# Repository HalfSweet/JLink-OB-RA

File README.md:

# JLink-OB-RA

该工程实现了SEGGER的J-Link-OB-RA4M2硬件设计，并加入了UART和SWD接口的硬件SWAP功能。

## KiCAD工程

该工程使用KiCAD设计，需要使用8.0以上版本打开。

## 版权申明

该工程的原始设计文件由SEGGER提供，本工程仅复刻硬件设计。其中运行的软件部分由SEGGER提供，本工程不提供任何软件支持。

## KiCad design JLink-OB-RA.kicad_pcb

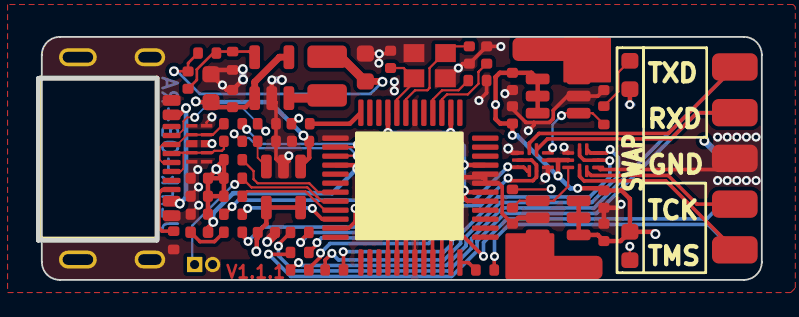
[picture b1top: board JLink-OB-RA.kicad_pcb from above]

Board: 4 copper layers, 40.1 x 13.3 mm, 57 parts (0 on the bottom side), 47 nets.

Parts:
C1, C4, C7, C8, C9, C13, C17: 0.1u; C_0402_1005Metric
C2, C3: 20p; C_0402_1005Metric
C5, C6: 50p; C_0402_1005Metric
C10: 22p; C_0402_1005Metric
C11, C16: 22u; C_0603_1608Metric
C12: 1u; C_0402_1005Metric
C14, C15, C18: 10u; C_0402_1005Metric
D1: LED; LED_0402_1005Metric
D2, D3: LED; LED_0603_1608Metric
J1: USB_C_Receptacle_USB2.0; USB-C-SMD_SHOU_TYPE-C-16P-CB1.6
J2: Conn_02x05_Counter_Clockwise; Conn_02x05_PinHeader_SMD
J3: Header; PinHeader_1x02_P1.00mm_Vertical
L1: 2.2u; L_1008_2520Metric
R1, R2, R5, R6, R7: 10k; R_0402_1005Metric
R3, R4: 27R; R_0402_1005Metric
R8, R19, R20: 1k; R_0402_1005Metric
R9, R10: 5.1k; R_0402_1005Metric
R11, R12, R13, R14, R15, R16: 150R; R_0402_1005Metric
R17: 100k; R_0402_1005Metric
R18: 22.1k; R_0402_1005Metric
R21: 6.8k; R_0402_1005Metric
TP1, TP2: TouchPad; Touch_SMD_BOX
U1: R7FA4M2AB3CFL#AA0; LQFP-48_7x7mm_P0.5mm
U2: ESD0524P_C2901307; DFN-10_L2.5-W1.0-P0.50-BL-A
U3, U4: TTP223; SOT-23-6
U5, U6: RS2227XUTQK10; WQFN-10_L1.8-W1.4-P0.40-BL
U7: MT3410; SOT-23-5
U8: MT9700; SOT-23-5
Y1: 12M; Crystal_SMD_2520-4Pin_2.5x2.0mm

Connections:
+3V3: C4.1, C7.1, C8.1, C9.1, C10.1, C11.1, C12.1, C13.1, C14.1, D1.2 (A), D2.2 (A), D3.2 (A), J2.8, L1.1, R2.1, R5.1, R6.1, R7.1, R17.1, U1.2 (VBATT), U1.9 (VCC_1), U1.16 (VCC_USB), U1.30 (VCC_2), U1.41 (VREFH), U1.42 (AVCC0), U1.45 (VREFH0), U3.4 (AHLB), U3.5 (VDD), U3.6 (TOG), U4.4 (AHLB), U4.5 (VDD), U4.6 (TOG), U5.9 (V+), U6.9 (V+)
+5V: C16.1, C17.1, C18.2, U7.1 (EN), U7.4 (VIN), U8.1 (VOUT)
/#RESET: J2.6, R15.2
/BOOT: J3.1, R6.2, U1.20 (P201/MD)
/EXTAL: C3.1, U1.8 (P212/EXTAL), Y1.3
/RA_RST: R5.2, U1.19 (RES)
/RX: U1.23 (P301), U6.4 (HSD1-), U6.7 (HSD2+)
/R_RX: J2.4, U6.1 (D+)
/R_TCK: J2.2, U5.2 (D-)
/R_TMS: J2.1, U5.1 (D+)
/R_TX: J2.5, U6.2 (D-)
/SWAP_SWD: R19.1, U3.1 (Q), U5.10 (S)
/SWAP_UART: R20.1, U4.1 (Q), U6.10 (S)
/TCK: R13.2, U5.5 (HSD1+), U5.6 (HSD2-)
/TDI: J2.9, U1.33 (P103)
/TDO: J2.10, R11.2
/TMS: R12.2, U5.4 (HSD1-), U5.7 (HSD2+)
/TRST: J2.7, R14.2
/TX: R16.1, U6.5 (HSD1+), U6.6 (HSD2-)
/USB_D+: J1.A6 (D+), J1.B6 (D+), R4.1, U2.4, U2.7
/USB_D-: J1.A7 (D-), J1.B7 (D-), R3.1, U2.2, U2.9
/XTAL: C2.1, U1.7 (P213/XTAL), Y1.1
GND: C1.1, C2.2, C3.2, C4.2, C5.2, C6.2, C7.2, C8.2, C9.2, C11.2, C12.2, C13.2, C14.2, C15.2, C16.2, C17.2, C18.1, J1.A1 (GND), J1.A12 (GND), J1.B1 (GND), J1.B12 (GND), J1.S1 (SHIELD), J2.3, J3.2, R1.1, R9.2, R10.2, R18.2, R21.1, U1.6 (VSS_1), U1.13 (VSS_USB), U1.31 (VSS_2), U1.43 (AVSS0/VREFL), U1.44 (VREFL0), U2.1, U2.3, U2.5, U2.6, U2.8, U2.10, U3.2 (VSS), U4.2 (VSS), U5.3 (GND), U5.8 (OE#), U6.3 (GND), U6.8 (OE#), U7.2 (GND), U8.2 (GND), Y1.2, Y1.4
unnamed: D1.1 (K), R8.2
unnamed: D2.1 (K), R19.2
unnamed: D3.1 (K), R20.2
unnamed: J1.A5 (CC1), R9.1
unnamed: J1.B5 (CC2), R10.1
unnamed: R11.1, U1.36 (P100)
unnamed: R12.1, U1.35 (P101)
unnamed: R13.1, U1.34 (P102)
unnamed: R14.1, U1.32 (P104)
unnamed: R8.1, U1.28 (P111)
unnamed: R15.1, U1.29 (P112)
unnamed: R7.2, U1.21 (P200)
unnamed: R16.2, U1.22 (P302)
unnamed: R2.2, U1.12 (P407)
unnamed: R3.2, U1.14 (USB_DM)
unnamed: R4.2, U1.15 (USB_DP)
unnamed: C1.2, U1.3 (VCL)
unnamed: R1.2, U1.4 (XCIN)
unnamed: C5.1, TP1.1, U3.3 (I)
unnamed: C6.1, TP2.1, U4.3 (I)
unnamed: C10.2, R17.2, R18.1, U7.5 (FB)
unnamed: L1.2, U7.3 (SW)
unnamed: R21.2, U8.3 (SET)
VBUS: C15.1, J1.A4 (VBUS), J1.A9 (VBUS), J1.B4 (VBUS), J1.B9 (VBUS), U8.4 (EN), U8.5 (VIN)

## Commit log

2023-11-30 init
2023-11-30 update: 更新为1.1.0
2024-07-26 fix: TDO和RST的丝印反了
2024-07-26 update: README
2024-07-26 update: 添加版权申明
2024-07-26 update: 更新版本
2024-07-26 fix: 版本号丝印的mask层未修改
